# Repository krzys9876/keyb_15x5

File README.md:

# Diy mechanical keyboard

This is a dump of all the files that I used to build my custom mech keyboard.

## Layout

To prepare the base layout I used [keyboard-layout-editor](http://www.keyboard-layout-editor.com/). 

I ended-up with [15x5 layout with split space](https://gist.github.com/krzys9876/6718b1eb58f1728975fdd1076bed487b). 
This was my key requirement since what I really wanted was a keyboard with mouse functions built-in. Now, using arrows as mouse movements and split keyboard as left-mid-right mouse buttons I do not need mouse at all. 
Well, maybe this is not the most usefull and ergonomic way to handle mouse but hey, this is all for fun, right?

I tweaked the layout several times since than. The only constraint is the location of the 4 2u keys: space(s) and Enter.

## PCB

I created a PCB and schematic sketch using excellent [klepcbgen tool](https://github.com/jeroen94704/klepcbgen). This was a good starting point to tweak the design to match my ideas. 
I had some experience in designing PCBs and electonic circuits in general (see my [ZX Spectrum Diy project](https://github.com/krzys9876/ZX_Spectrum_diy) so it was quite easy. 

But all in all it was not that great - I totally failed with LEDs since I did not use proper footprint for WS2812B-2020 leds. So after I got the boards from JLCPBC it turned out that I cannot use LEDs at all. 
What you see now is a revised version that I did not (yet) put into production.

Other than that the board worked perfectly.

## Firmware

This is a fun project so I would not use any ready-to-use firmware. Anyway I don't think that any of available firmwares would allow me to use mouse. 
So I wrote my own simple version of keyboard handler using Arduino Micro templates and examples. The firmware uses [HID-project](https://github.com/NicoHood/HID).

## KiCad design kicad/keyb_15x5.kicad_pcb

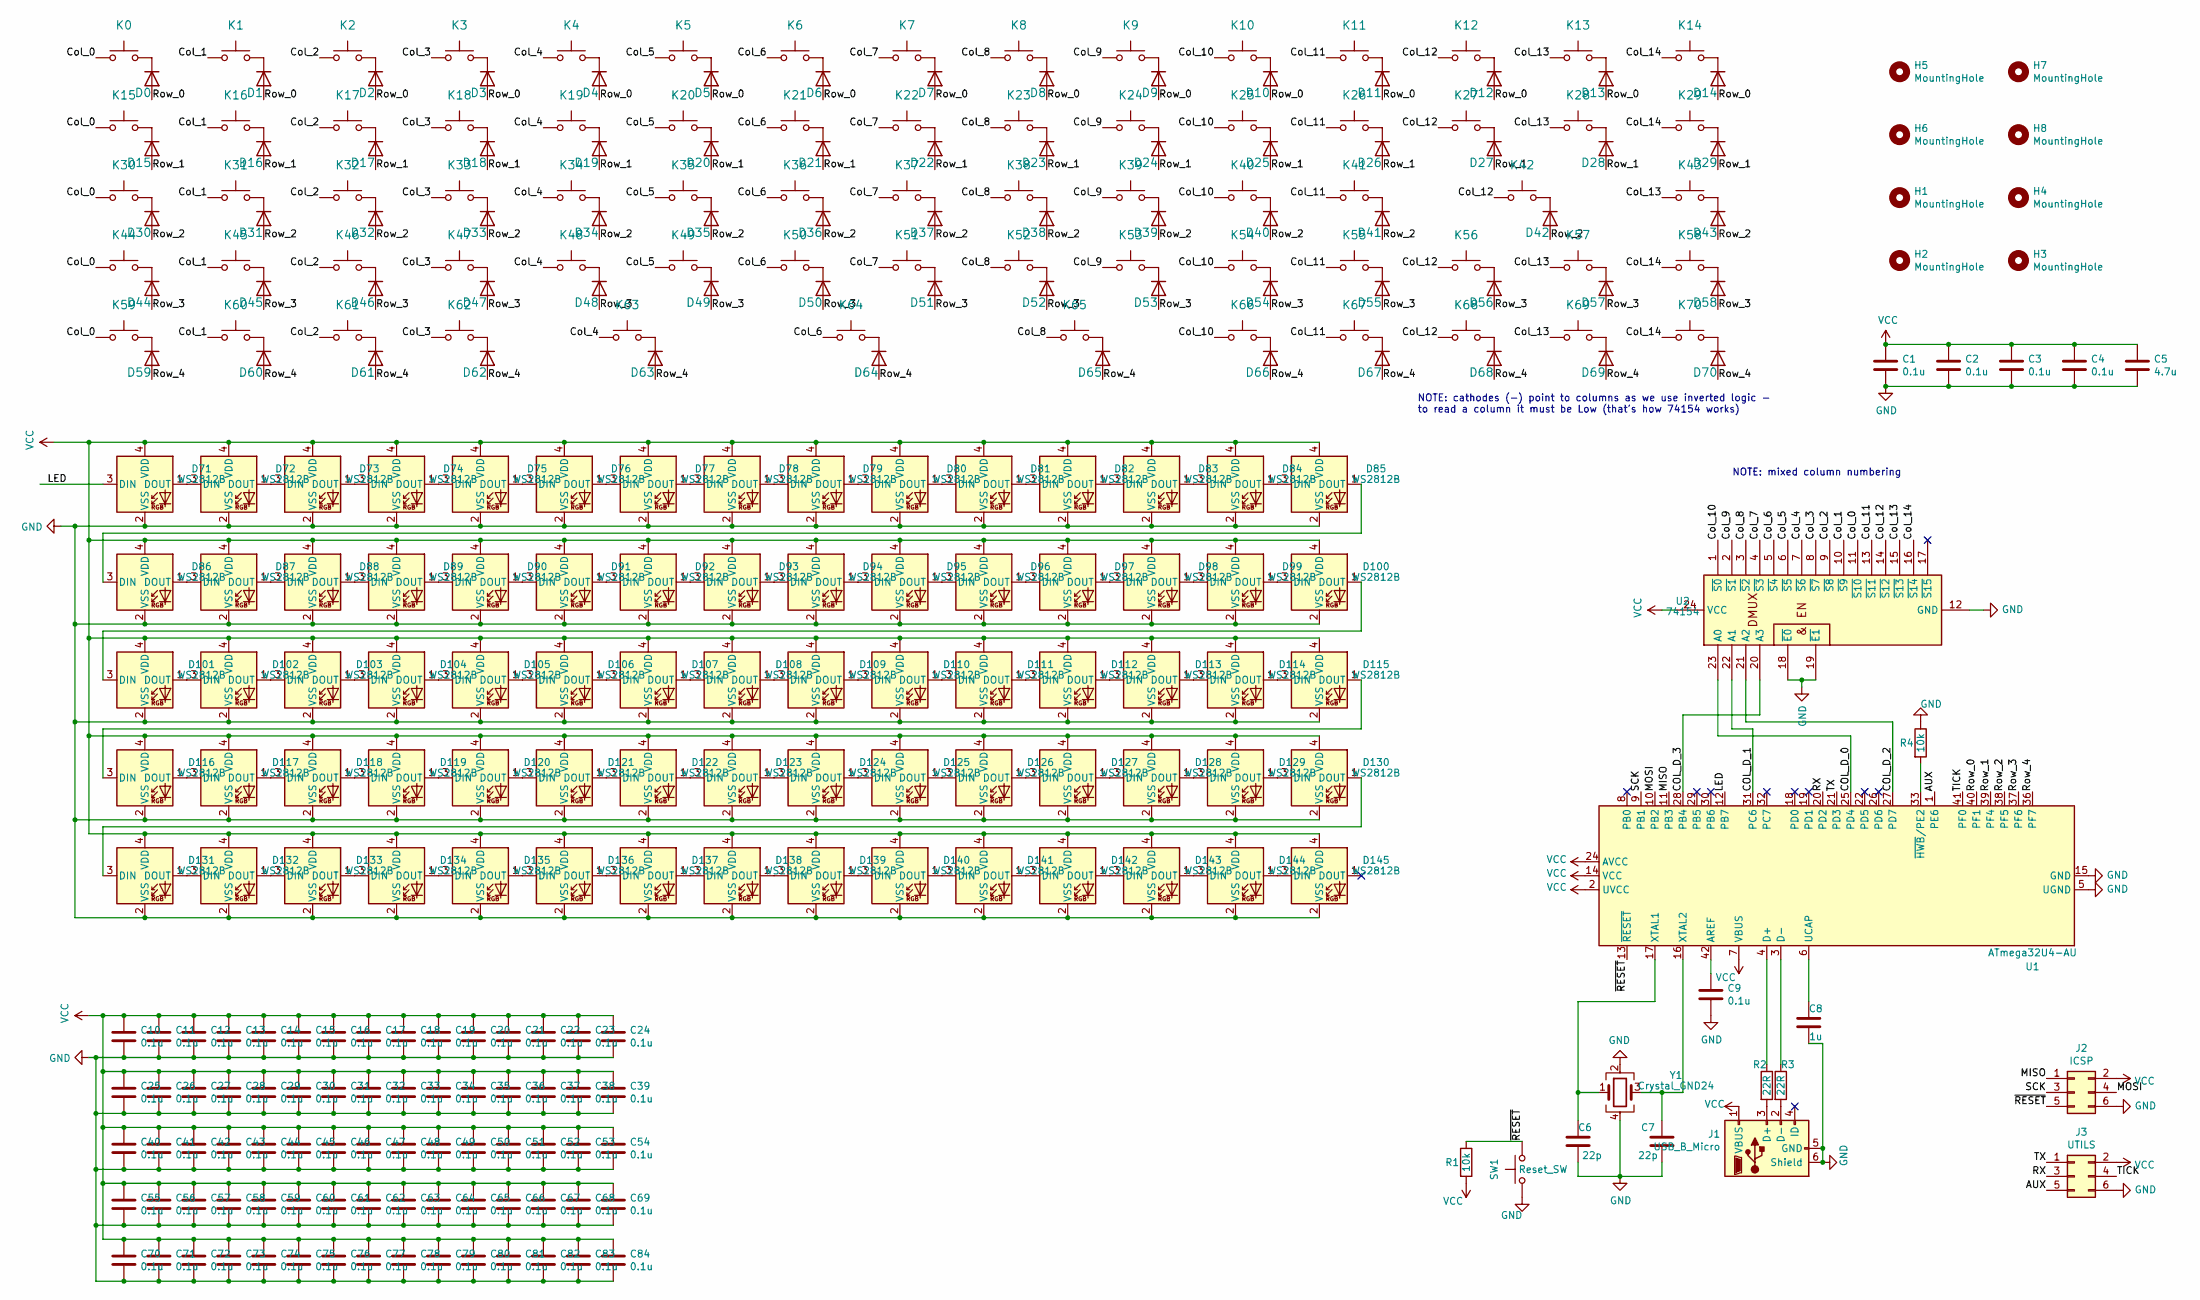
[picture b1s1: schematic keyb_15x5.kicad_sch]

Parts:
C1, C2, C3, C4, C9, C10, C11, C12, C13, C14, C15, C16, C17, C18, C19, C20, C21, C22, C23, C24, C25, C26, C27, C28, C29, C30, C31, C32, C33, C34, C35, C36, C37, C38, C39, C40, C41, C42, C43, C44, C45, C46, C47, C48, C49, C50, C51, C52, C53, C54, C55, C56, C57, C58, C59, C60, C61, C62, C63, C64, C65, C66, C67, C68, C69, C70, C71, C72, C73, C74, C75, C76, C77, C78, C79, C80, C81, C82, C83, C84: 0.1u; C_0805_2012Metric
C5: 4.7u; C_0805_2012Metric
C6, C7: 22p; C_0805_2012Metric
C8: 1u; C_0805_2012Metric
D0, D1, D2, D3, D4, D5, D6, D7, D8, D9, D10, D11, D12, D13, D14, D15, D16, D17, D18, D19, D20, D21, D22, D23, D24, D25, D26, D27, D28, D29, D30, D31, D32, D33, D34, D35, D36, D37, D38, D39, D40, D41, D42, D43, D44, D45, D46, D47, D48, D49, D50, D51, D52, D53, D54, D55, D56, D57, D58, D59, D60, D61, D62, D63, D64, D65, D66, D67, D68, D69, D70: D; D_0805_2012Metric_Pad1.15x1.40mm_HandSolder
D71, D72, D73, D74, D75, D76, D77, D78, D79, D80, D81, D82, D83, D84, D85, D86, D87, D88, D89, D90, D91, D92, D93, D94, D95, D96, D97, D98, D99, D100, D101, D102, D103, D104, D105, D106, D107, D108, D109, D110, D111, D112, D113, D114, D115, D116, D117, D118, D119, D120, D121, D122, D123, D124, D125, D126, D127, D128, D129, D130, D131, D132, D133, D134, D135, D136, D137, D138, D139, D140, D141, D142, D143, D144, D145: WS2812B; LED_WS2812B_PLCC4_5.0x5.0mm_P3.2mm
H1, H2, H3, H4, H5, H6, H7, H8: MountingHole; MountingHole_3.2mm_M3_DIN965
J1: USB_B_Micro; USB_Micro-B_Amphenol_10104110_Horizontal
J2: ICSP; PinHeader_2x03_P2.54mm_Vertical
J3: UTILS; PinHeader_2x03_P2.54mm_Vertical
K0, K1, K2, K3, K4, K5, K6, K7, K8, K9, K10, K11, K12, K13, K14, K15, K16, K17, K18, K19, K20, K21, K22, K23, K24, K25, K26, K27, K28, K29, K30, K31, K32, K33, K34, K35, K36, K37, K38, K39, K40, K41, K42, K43, K44, K45, K46, K47, K48, K49, K50, K51, K52, K53, K54, K55, K56, K57, K58, K59, K60, K61, K62, K63, K64, K65, K66, K67, K68, K69, K70: KEYSW; Kailh_socket_MX_platemount
R1, R4: 10k; R_0805_2012Metric_Pad1.15x1.40mm_HandSolder
R2, R3: 22R; R_0805_2012Metric_Pad1.15x1.40mm_HandSolder
SW1: Reset_SW; SW_Push_1P1T_NO_6x6mm_H9.5mm
U1: ATmega32U4-AU; TQFP-44_10x10mm_P0.8mm
U2: 74154; SOIC-24W_7.5x15.4mm_P1.27mm
Y1: Crystal_GND24; Crystal_SMD_3225-4Pin_3.2x2.5mm_HandSoldering

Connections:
/AUX: J3.5, U1.1 (PE6)
/COL_D_0: U1.25 (PD4), U2.23 (A0)
/COL_D_1: U1.31 (PC6), U2.22 (A1)
/COL_D_2: U1.27 (PD7), U2.21 (A2)
/COL_D_3: U1.28 (PB4), U2.20 (A3)
/Col_0: K0.1, K15.1, K30.1, K44.1, K59.1, U2.11 (~S10)
/Col_1: K1.1, K16.1, K31.1, K45.1, K60.1, U2.10 (~S9)
/Col_2: K2.1, K17.1, K32.1, K46.1, K61.1, U2.9 (~S8)
/Col_3: K3.1, K18.1, K33.1, K47.1, K62.1, U2.8 (~S7)
/Col_4: K4.1, K19.1, K34.1, K48.1, K63.1, U2.7 (~S6)
/Col_5: K5.1, K20.1, K35.1, K49.1, U2.6 (~S5)
/Col_6: K6.1, K21.1, K36.1, K50.1, K64.1, U2.5 (~S4)
/Col_7: K7.1, K22.1, K37.1, K51.1, U2.4 (~S3)
/Col_8: K8.1, K23.1, K38.1, K52.1, K65.1, U2.3 (~S2)
/Col_9: K9.1, K24.1, K39.1, K53.1, U2.2 (~S1)
/Col_10: K10.1, K25.1, K40.1, K54.1, K66.1, U2.1 (~S0)
/Col_11: K11.1, K26.1, K41.1, K55.1, K67.1, U2.13 (~S11)
/Col_12: K12.1, K27.1, K42.1, K56.1, K68.1, U2.14 (~S12)
/Col_13: K13.1, K28.1, K43.1, K57.1, K69.1, U2.15 (~S13)
/Col_14: K14.1, K29.1, K58.1, K70.1, U2.16 (~S14)
/LED: D71.3 (DIN), U1.12 (PB7)
/MISO: J2.1, U1.11 (PB3)
/MOSI: J2.4, U1.10 (PB2)
/RX: J3.3, U1.20 (PD2)
/Row_0: D0.2 (A), D1.2 (A), D2.2 (A), D3.2 (A), D4.2 (A), D5.2 (A), D6.2 (A), D7.2 (A), D8.2 (A), D9.2 (A), D10.2 (A), D11.2 (A), D12.2 (A), D13.2 (A), D14.2 (A), U1.40 (PF1)
/Row_1: D15.2 (A), D16.2 (A), D17.2 (A), D18.2 (A), D19.2 (A), D20.2 (A), D21.2 (A), D22.2 (A), D23.2 (A), D24.2 (A), D25.2 (A), D26.2 (A), D27.2 (A), D28.2 (A), D29.2 (A), U1.39 (PF4)
/Row_2: D30.2 (A), D31.2 (A), D32.2 (A), D33.2 (A), D34.2 (A), D35.2 (A), D36.2 (A), D37.2 (A), D38.2 (A), D39.2 (A), D40.2 (A), D41.2 (A), D42.2 (A), D43.2 (A), U1.38 (PF5)
/Row_3: D44.2 (A), D45.2 (A), D46.2 (A), D47.2 (A), D48.2 (A), D49.2 (A), D50.2 (A), D51.2 (A), D52.2 (A), D53.2 (A), D54.2 (A), D55.2 (A), D56.2 (A), D57.2 (A), D58.2 (A), U1.37 (PF6)
/Row_4: D59.2 (A), D60.2 (A), D61.2 (A), D62.2 (A), D63.2 (A), D64.2 (A), D65.2 (A), D66.2 (A), D67.2 (A), D68.2 (A), D69.2 (A), D70.2 (A), U1.36 (PF7)
/SCK: J2.3, U1.9 (PB1)
/TICK: J3.4, U1.41 (PF0)
/TX: J3.1, U1.21 (PD3)
/~RESET: J2.5, R1.1, SW1.2, U1.13 (~RESET)
GND: C1.2, C2.2, C3.2, C4.2, C5.2, C6.2, C7.2, C8.2, C9.2, C10.2, C11.2, C12.2, C13.2, C14.2, C15.2, C16.2, C17.2, C18.2, C19.2, C20.2, C21.2, C22.2, C23.2, C24.2, C25.2, C26.2, C27.2, C28.2, C29.2, C30.2, C31.2, C32.2, C33.2, C34.2, C35.2, C36.2, C37.2, C38.2, C39.2, C40.2, C41.2, C42.2, C43.2, C44.2, C45.2, C46.2, C47.2, C48.2, C49.2, C50.2, C51.2, C52.2, C53.2, C54.2, C55.2, C56.2, C57.2, C58.2, C59.2, C60.2, C61.2, C62.2, C63.2, C64.2, C65.2, C66.2, C67.2, C68.2, C69.2, C70.2, C71.2, C72.2, C73.2, C74.2, C75.2, C76.2, C77.2, C78.2, C79.2, C80.2, C81.2, C82.2, C83.2, C84.2, D71.2 (VSS), D72.2 (VSS), D73.2 (VSS), D74.2 (VSS), D75.2 (VSS), D76.2 (VSS), D77.2 (VSS), D78.2 (VSS), D79.2 (VSS), D80.2 (VSS), D81.2 (VSS), D82.2 (VSS), D83.2 (VSS), D84.2 (VSS), D85.2 (VSS), D86.2 (VSS), D87.2 (VSS), D88.2 (VSS), D89.2 (VSS), D90.2 (VSS), D91.2 (VSS), D92.2 (VSS), D93.2 (VSS), D94.2 (VSS), D95.2 (VSS), D96.2 (VSS), D97.2 (VSS), D98.2 (VSS), D99.2 (VSS), D100.2 (VSS), D101.2 (VSS), D102.2 (VSS), D103.2 (VSS), D104.2 (VSS), D105.2 (VSS), D106.2 (VSS), D107.2 (VSS), D108.2 (VSS), D109.2 (VSS), D110.2 (VSS), D111.2 (VSS), D112.2 (VSS), D113.2 (VSS), D114.2 (VSS), D115.2 (VSS), D116.2 (VSS), D117.2 (VSS), D118.2 (VSS), D119.2 (VSS), D120.2 (VSS), D121.2 (VSS), D122.2 (VSS), D123.2 (VSS), D124.2 (VSS), D125.2 (VSS), D126.2 (VSS), D127.2 (VSS), D128.2 (VSS), D129.2 (VSS), D130.2 (VSS), D131.2 (VSS), D132.2 (VSS), D133.2 (VSS), D134.2 (VSS), D135.2 (VSS), D136.2 (VSS), D137.2 (VSS), D138.2 (VSS), D139.2 (VSS), D140.2 (VSS), D141.2 (VSS), D142.2 (VSS), D143.2 (VSS), D144.2 (VSS), D145.2 (VSS), J1.5 (GND), J1.6 (Shield), J2.6, J3.6, R4.1, SW1.1, U1.5 (UGND), U1.15 (GND), U1.23 (GND), U1.35 (GND), U1.43 (GND), U2.12 (GND), U2.18 (~E0), U2.19 (~E1), Y1.2, Y1.4
unnamed: D0.1 (K), K0.2
unnamed: D1.1 (K), K1.2
unnamed: D2.1 (K), K2.2
unnamed: D3.1 (K), K3.2
unnamed: D4.1 (K), K4.2
unnamed: D5.1 (K), K5.2
unnamed: D6.1 (K), K6.2
unnamed: D7.1 (K), K7.2
unnamed: D8.1 (K), K8.2
unnamed: D9.1 (K), K9.2
unnamed: D10.1 (K), K10.2
unnamed: D11.1 (K), K11.2
unnamed: D12.1 (K), K12.2
unnamed: D13.1 (K), K13.2
unnamed: D14.1 (K), K14.2
unnamed: D15.1 (K), K15.2
unnamed: D16.1 (K), K16.2
unnamed: D17.1 (K), K17.2
unnamed: D18.1 (K), K18.2
unnamed: D19.1 (K), K19.2
unnamed: D20.1 (K), K20.2
unnamed: D21.1 (K), K21.2
unnamed: D22.1 (K), K22.2
unnamed: D23.1 (K), K23.2
unnamed: D24.1 (K), K24.2
unnamed: D25.1 (K), K25.2
unnamed: D26.1 (K), K26.2
unnamed: D27.1 (K), K27.2
unnamed: D28.1 (K), K28.2
unnamed: D29.1 (K), K29.2
unnamed: D30.1 (K), K30.2
unnamed: D31.1 (K), K31.2
unnamed: D32.1 (K), K32.2
unnamed: D33.1 (K), K33.2
unnamed: D34.1 (K), K34.2
unnamed: D35.1 (K), K35.2
unnamed: D36.1 (K), K36.2
unnamed: D37.1 (K), K37.2
unnamed: D38.1 (K), K38.2
unnamed: D39.1 (K), K39.2
unnamed: D40.1 (K), K40.2
unnamed: D41.1 (K), K41.2
unnamed: D42.1 (K), K42.2
unnamed: D43.1 (K), K43.2
unnamed: D44.1 (K), K44.2
unnamed: D45.1 (K), K45.2
unnamed: D46.1 (K), K46.2
unnamed: D47.1 (K), K47.2
unnamed: D48.1 (K), K48.2
unnamed: D49.1 (K), K49.2
unnamed: D50.1 (K), K50.2
unnamed: D51.1 (K), K51.2
unnamed: D52.1 (K), K52.2
unnamed: D53.1 (K), K53.2
unnamed: D54.1 (K), K54.2
unnamed: D55.1 (K), K55.2
unnamed: D56.1 (K), K56.2
unnamed: D57.1 (K), K57.2
unnamed: D58.1 (K), K58.2
unnamed: D59.1 (K), K59.2
unnamed: D60.1 (K), K60.2
unnamed: D61.1 (K), K61.2
unnamed: D62.1 (K), K62.2
unnamed: D63.1 (K), K63.2
unnamed: D64.1 (K), K64.2
unnamed: D65.1 (K), K65.2
unnamed: D66.1 (K), K66.2
unnamed: D67.1 (K), K67.2
unnamed: D68.1 (K), K68.2
unnamed: D69.1 (K), K69.2
unnamed: D70.1 (K), K70.2
unnamed: D71.1 (DOUT), D72.3 (DIN)
unnamed: D72.1 (DOUT), D73.3 (DIN)
unnamed: D73.1 (DOUT), D74.3 (DIN)
unnamed: D74.1 (DOUT), D75.3 (DIN)
unnamed: D75.1 (DOUT), D76.3 (DIN)
unnamed: D76.1 (DOUT), D77.3 (DIN)
unnamed: D77.1 (DOUT), D78.3 (DIN)
unnamed: D78.1 (DOUT), D79.3 (DIN)
unnamed: D79.1 (DOUT), D80.3 (DIN)
unnamed: D80.1 (DOUT), D81.3 (DIN)
unnamed: D81.1 (DOUT), D82.3 (DIN)
unnamed: D82.1 (DOUT), D83.3 (DIN)
unnamed: D83.1 (DOUT), D84.3 (DIN)
unnamed: D84.1 (DOUT), D85.3 (DIN)
unnamed: D85.1 (DOUT), D86.3 (DIN)
unnamed: D86.1 (DOUT), D87.3 (DIN)
unnamed: D87.1 (DOUT), D88.3 (DIN)
unnamed: D88.1 (DOUT), D89.3 (DIN)
unnamed: D89.1 (DOUT), D90.3 (DIN)
unnamed: D90.1 (DOUT), D91.3 (DIN)
unnamed: D91.1 (DOUT), D92.3 (DIN)
unnamed: D92.1 (DOUT), D93.3 (DIN)
unnamed: D93.1 (DOUT), D94.3 (DIN)
unnamed: D94.1 (DOUT), D95.3 (DIN)
unnamed: D95.1 (DOUT), D96.3 (DIN)
unnamed: D96.1 (DOUT), D97.3 (DIN)
unnamed: D97.1 (DOUT), D98.3 (DIN)
unnamed: D98.1 (DOUT), D99.3 (DIN)
unnamed: D99.1 (DOUT), D100.3 (DIN)
unnamed: D100.1 (DOUT), D101.3 (DIN)
unnamed: D101.1 (DOUT), D102.3 (DIN)
unnamed: D102.1 (DOUT), D103.3 (DIN)
unnamed: D103.1 (DOUT), D104.3 (DIN)
unnamed: D104.1 (DOUT), D105.3 (DIN)
unnamed: D105.1 (DOUT), D106.3 (DIN)
unnamed: D106.1 (DOUT), D107.3 (DIN)
unnamed: D107.1 (DOUT), D108.3 (DIN)
unnamed: D108.1 (DOUT), D109.3 (DIN)
unnamed: D109.1 (DOUT), D110.3 (DIN)
unnamed: D110.1 (DOUT), D111.3 (DIN)
unnamed: D111.1 (DOUT), D112.3 (DIN)
unnamed: D112.1 (DOUT), D113.3 (DIN)
unnamed: D113.1 (DOUT), D114.3 (DIN)
unnamed: D114.1 (DOUT), D115.3 (DIN)
unnamed: D115.1 (DOUT), D116.3 (DIN)
unnamed: D116.1 (DOUT), D117.3 (DIN)
unnamed: D117.1 (DOUT), D118.3 (DIN)
unnamed: D118.1 (DOUT), D119.3 (DIN)
unnamed: D119.1 (DOUT), D120.3 (DIN)
unnamed: D120.1 (DOUT), D121.3 (DIN)
unnamed: D121.1 (DOUT), D122.3 (DIN)
unnamed: D122.1 (DOUT), D123.3 (DIN)
unnamed: D123.1 (DOUT), D124.3 (DIN)
unnamed: D124.1 (DOUT), D125.3 (DIN)
unnamed: D125.1 (DOUT), D126.3 (DIN)
unnamed: D126.1 (DOUT), D127.3 (DIN)
unnamed: D127.1 (DOUT), D128.3 (DIN)
unnamed: D128.1 (DOUT), D129.3 (DIN)
unnamed: D129.1 (DOUT), D130.3 (DIN)
unnamed: D130.1 (DOUT), D131.3 (DIN)
unnamed: D131.1 (DOUT), D132.3 (DIN)
unnamed: D132.1 (DOUT), D133.3 (DIN)
unnamed: D133.1 (DOUT), D134.3 (DIN)
unnamed: D134.1 (DOUT), D135.3 (DIN)
unnamed: D135.1 (DOUT), D136.3 (DIN)
unnamed: D136.1 (DOUT), D137.3 (DIN)
unnamed: D137.1 (DOUT), D138.3 (DIN)
unnamed: D138.1 (DOUT), D139.3 (DIN)
unnamed: D139.1 (DOUT), D140.3 (DIN)
unnamed: D140.1 (DOUT), D141.3 (DIN)
unnamed: D141.1 (DOUT), D142.3 (DIN)
unnamed: D142.1 (DOUT), D143.3 (DIN)
unnamed: D143.1 (DOUT), D144.3 (DIN)
unnamed: D144.1 (DOUT), D145.3 (DIN)
unnamed: J1.3 (D+), R2.2
unnamed: J1.2 (D-), R3.2
unnamed: C9.1, U1.42 (AREF)
unnamed: R2.1, U1.4 (D+)
unnamed: R3.1, U1.3 (D-)
unnamed: C8.1, U1.6 (UCAP)
unnamed: C6.1, U1.17 (XTAL1), Y1.1
unnamed: C7.1, U1.16 (XTAL2), Y1.3
unnamed: R4.2, U1.33 (~HWB/PE2)
VCC: C1.1, C2.1, C3.1, C4.1, C5.1, C10.1, C11.1, C12.1, C13.1, C14.1, C15.1, C16.1, C17.1, C18.1, C19.1, C20.1, C21.1, C22.1, C23.1, C24.1, C25.1, C26.1, C27.1, C28.1, C29.1, C30.1, C31.1, C32.1, C33.1, C34.1, C35.1, C36.1, C37.1, C38.1, C39.1, C40.1, C41.1, C42.1, C43.1, C44.1, C45.1, C46.1, C47.1, C48.1, C49.1, C50.1, C51.1, C52.1, C53.1, C54.1, C55.1, C56.1, C57.1, C58.1, C59.1, C60.1, C61.1, C62.1, C63.1, C64.1, C65.1, C66.1, C67.1, C68.1, C69.1, C70.1, C71.1, C72.1, C73.1, C74.1, C75.1, C76.1, C77.1, C78.1, C79.1, C80.1, C81.1, C82.1, C83.1, C84.1, D71.4 (VDD), D72.4 (VDD), D73.4 (VDD), D74.4 (VDD), D75.4 (VDD), D76.4 (VDD), D77.4 (VDD), D78.4 (VDD), D79.4 (VDD), D80.4 (VDD), D81.4 (VDD), D82.4 (VDD), D83.4 (VDD), D84.4 (VDD), D85.4 (VDD), D86.4 (VDD), D87.4 (VDD), D88.4 (VDD), D89.4 (VDD), D90.4 (VDD), D91.4 (VDD), D92.4 (VDD), D93.4 (VDD), D94.4 (VDD), D95.4 (VDD), D96.4 (VDD), D97.4 (VDD), D98.4 (VDD), D99.4 (VDD), D100.4 (VDD), D101.4 (VDD), D102.4 (VDD), D103.4 (VDD), D104.4 (VDD), D105.4 (VDD), D106.4 (VDD), D107.4 (VDD), D108.4 (VDD), D109.4 (VDD), D110.4 (VDD), D111.4 (VDD), D112.4 (VDD), D113.4 (VDD), D114.4 (VDD), D115.4 (VDD), D116.4 (VDD), D117.4 (VDD), D118.4 (VDD), D119.4 (VDD), D120.4 (VDD), D121.4 (VDD), D122.4 (VDD), D123.4 (VDD), D124.4 (VDD), D125.4 (VDD), D126.4 (VDD), D127.4 (VDD), D128.4 (VDD), D129.4 (VDD), D130.4 (VDD), D131.4 (VDD), D132.4 (VDD), D133.4 (VDD), D134.4 (VDD), D135.4 (VDD), D136.4 (VDD), D137.4 (VDD), D138.4 (VDD), D139.4 (VDD), D140.4 (VDD), D141.4 (VDD), D142.4 (VDD), D143.4 (VDD), D144.4 (VDD), D145.4 (VDD), J1.1 (VBUS), J2.2, J3.2, R1.2, U1.2 (UVCC), U1.7 (VBUS), U1.14 (VCC), U1.24 (AVCC), U1.34 (VCC), U1.44 (AVCC), U2.24 (VCC)

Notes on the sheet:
NOTE: mixed column numbering
NOTE: cathodes (-) point to columns as we use inverted logic - to read a column it must be Low (that's how 74154 works)

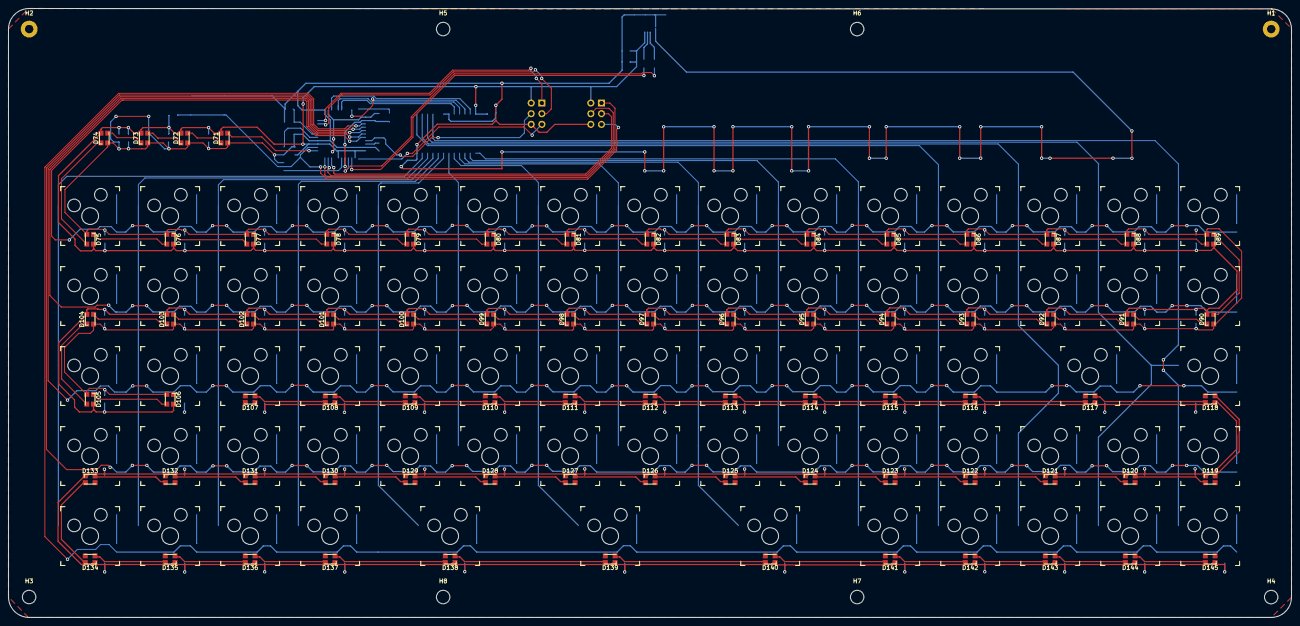
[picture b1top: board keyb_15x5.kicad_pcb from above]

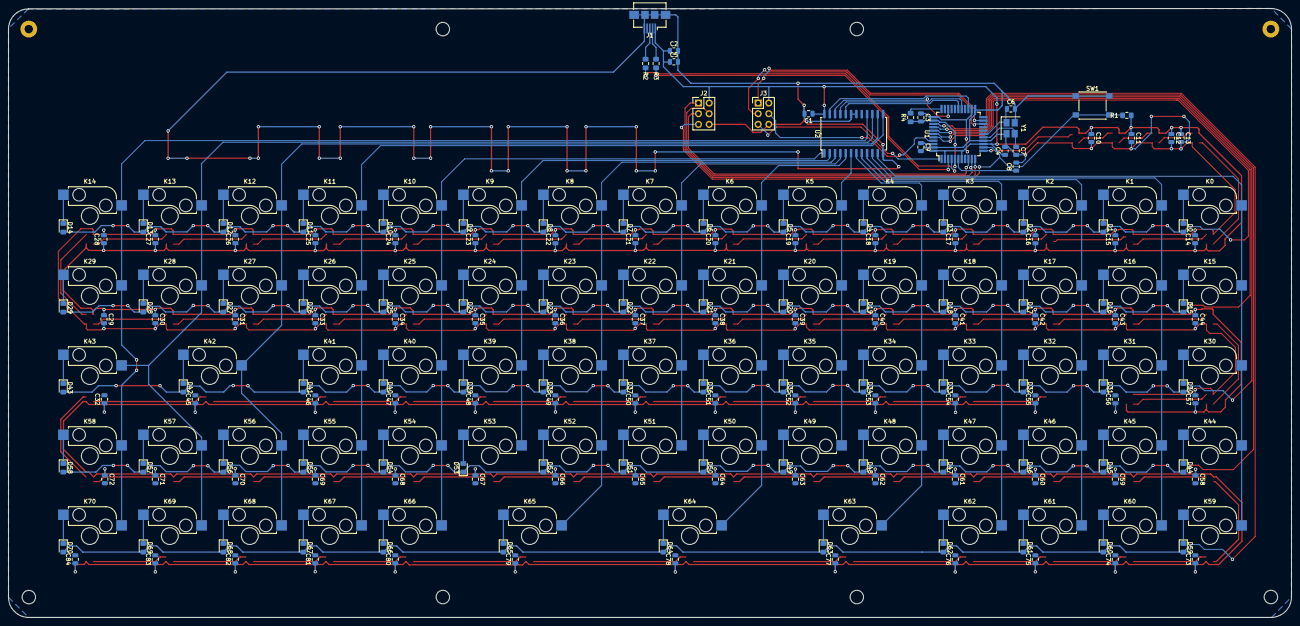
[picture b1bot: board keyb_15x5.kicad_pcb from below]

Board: 2 copper layers, 305.5 x 145.0 mm, 320 parts (166 on the bottom side), 189 nets.

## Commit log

2023-10-12 copy local files
2023-10-12 press and hold FN to switch from layer 0 to 1
2023-10-12 add separate mouse button (next to left Shiht)
2023-10-12 handle mouse button, correct wheel direction
2023-10-12 handle all function keys and mouse using override logic (the two override functions)
2023-10-12 remove FN codes from keyboard map - use only oferride logic to handle special keys and mouse
2023-10-12 correct mouse move speed
2023-10-12 set layer 0 when no key is pressed
2023-10-20 move arrow keys to the right
